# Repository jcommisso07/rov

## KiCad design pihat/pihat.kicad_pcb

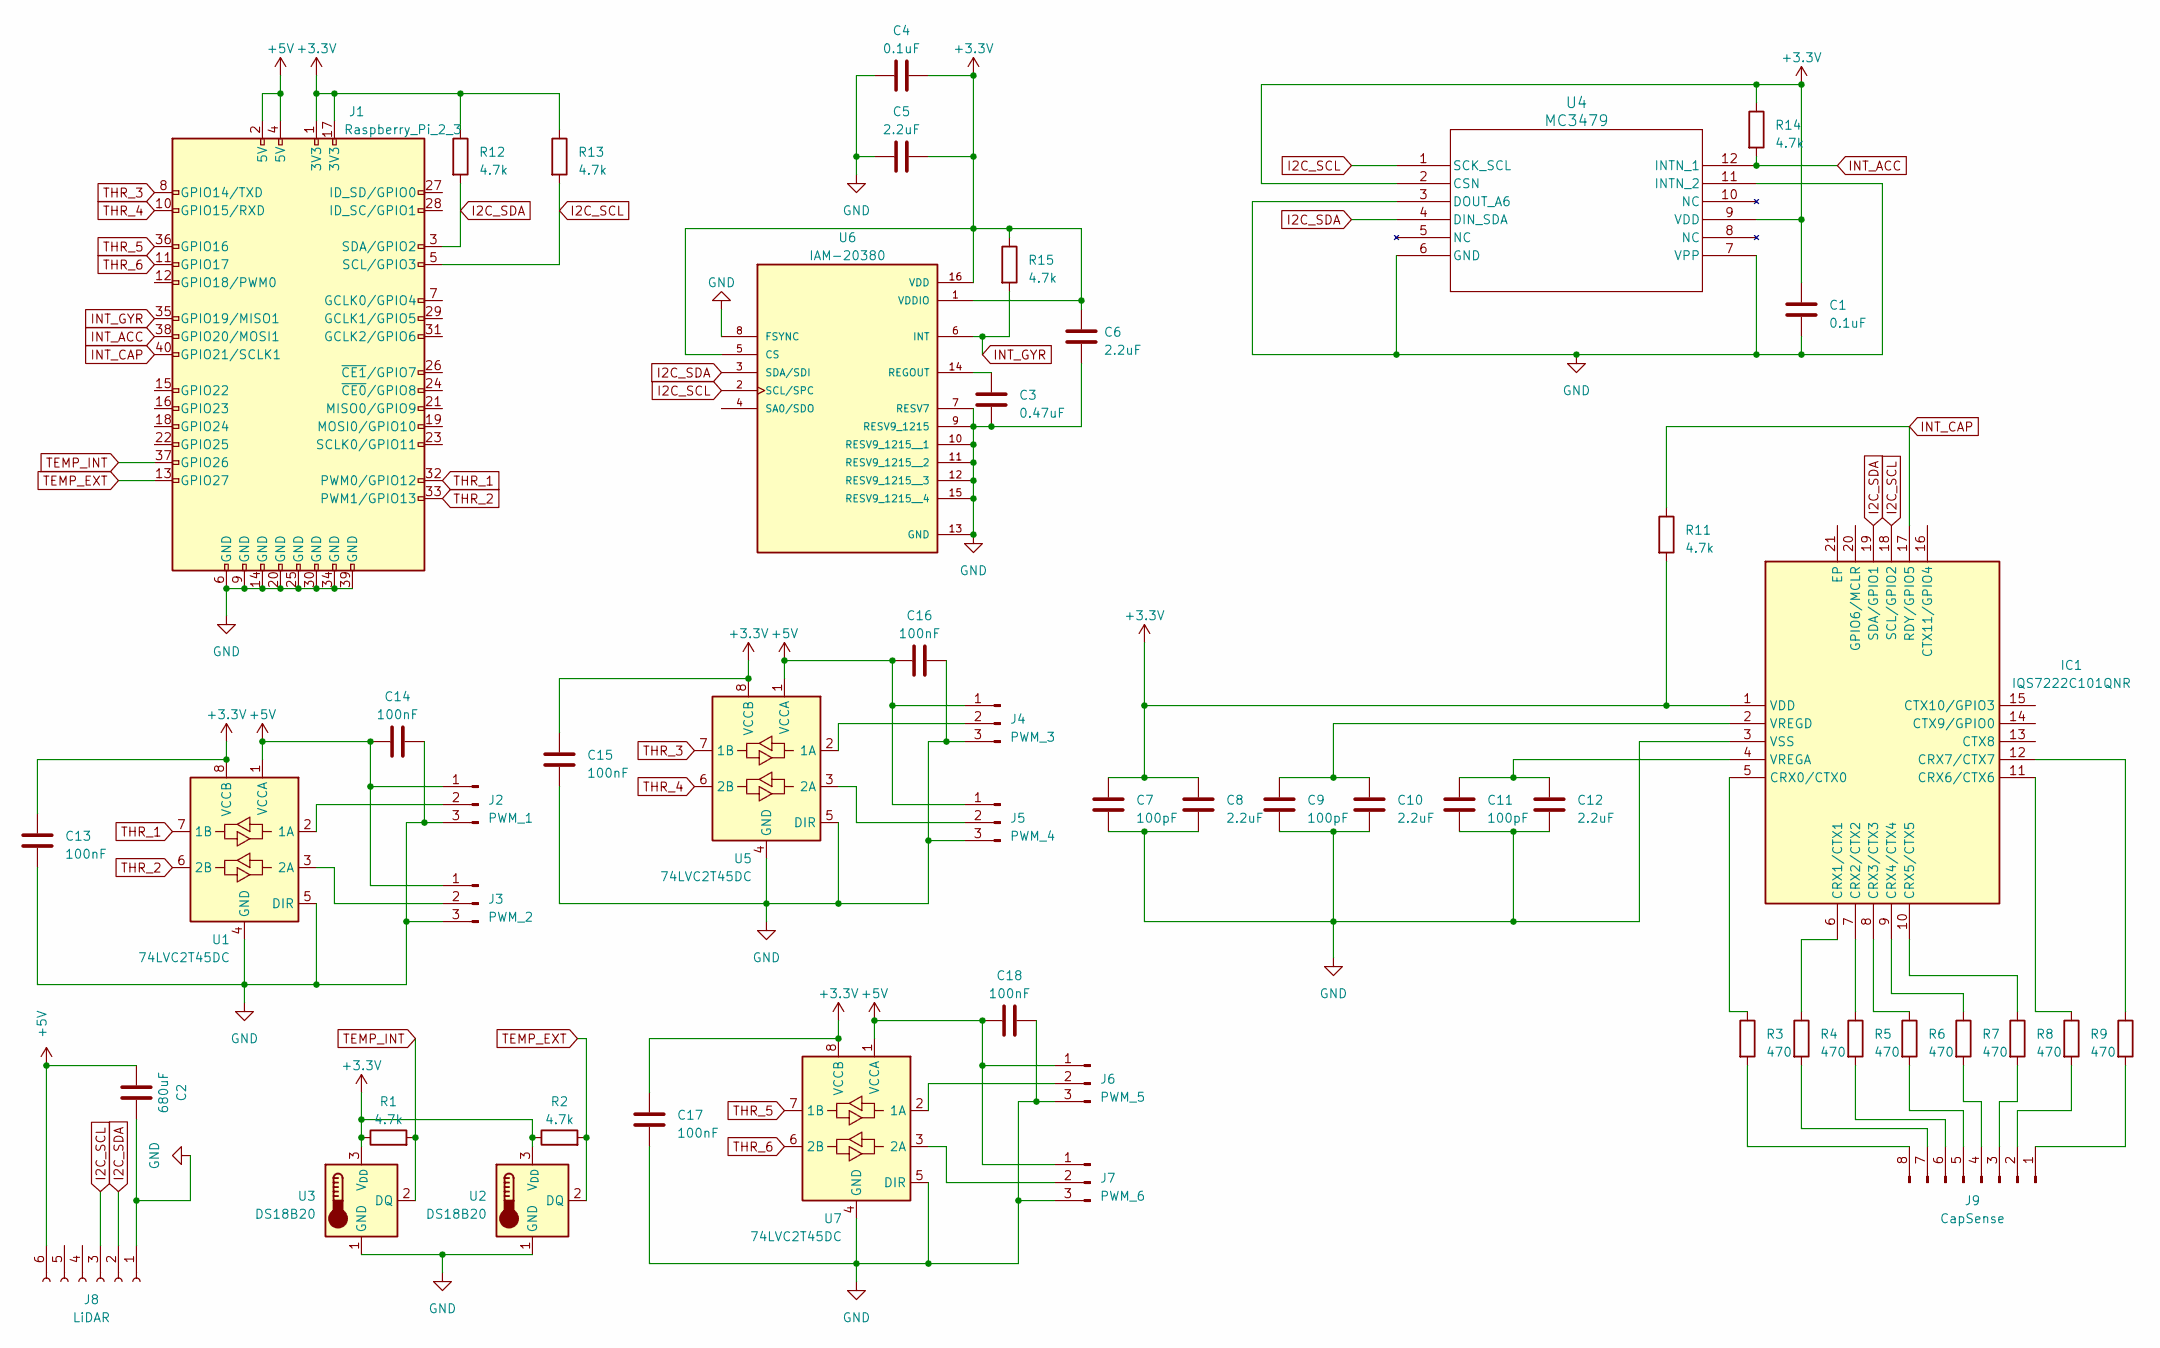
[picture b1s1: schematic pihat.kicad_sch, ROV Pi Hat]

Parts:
C1, C4: 0.1uF; C_0805_2012Metric
C2: 680uF; C_0805_2012Metric
C3: 0.47uF; C_0805_2012Metric
C5, C6, C8, C10, C12: 2.2uF; C_0805_2012Metric
C7, C9, C11: 100pF; C_0805_2012Metric
C13, C14, C15, C16, C17, C18: 100nF; C_0805_2012Metric
IC1: IQS7222C101QNR; QFN40P300X300X60-21N; Mouser Part Number 957-IQS7222C101QNR
J1: Raspberry_Pi_2_3; PinSocket_2x20_P2.54mm_Vertical
J2: PWM_1; PinHeader_1x03_P2.54mm_Vertical
J3: PWM_2; PinHeader_1x03_P2.54mm_Vertical
J4: PWM_3; PinHeader_1x03_P2.54mm_Vertical
J5: PWM_4; PinHeader_1x03_P2.54mm_Vertical
J6: PWM_5; PinHeader_1x03_P2.54mm_Vertical
J7: PWM_6; PinHeader_1x03_P2.54mm_Vertical
J8: LiDAR; PinHeader_1x06_P2.54mm_Vertical
J9: CapSense; PinHeader_1x08_P2.54mm_Vertical
R1, R2, R11, R12, R13, R14, R15: 4.7k; R_0603_1608Metric
R3, R4, R5, R6, R7, R8, R9, R10: 470; R_0603_1608Metric
U1, U5, U7: 74LVC2T45DC; VSSOP-8_2.3x2mm_P0.5mm
U2, U3: DS18B20; PinHeader_1x03_P2.54mm_Vertical
U4: MC3479; MC3479_MEM
U6: IAM-20380; PQFN50P300X300X80-16N

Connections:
+3.3V: C1.1, C4.2, C5.2, C6.2, C7.1, C8.1, C13.1, C15.1, C17.1, IC1.1 (VDD), J1.1 (3V3), J1.17 (3V3), R1.1, R2.1, R11.2, R12.1, R13.1, R14.1, R15.1, U1.8 (VCCB), U2.3 (V_{DD}), U3.3 (V_{DD}), U4.2 (CSN), U4.9 (VDD), U5.8 (VCCB), U6.1 (VDDIO), U6.5 (CS), U6.16 (VDD), U7.8 (VCCB)
+5V: C2.1, C14.1, C16.1, C18.1, J1.2 (5V), J1.4 (5V), J2.1, J3.1, J4.1, J5.1, J6.1, J7.1, J8.6, U1.1 (VCCA), U5.1 (VCCA), U7.1 (VCCA)
GND: C1.2, C2.2, C3.2, C4.1, C5.1, C6.1, C7.2, C8.2, C9.2, C10.2, C11.2, C12.2, C13.2, C14.2, C15.2, C16.2, C17.2, C18.2, IC1.3 (VSS), J1.6 (GND), J1.9 (GND), J1.14 (GND), J1.20 (GND), J1.25 (GND), J1.30 (GND), J1.34 (GND), J1.39 (GND), J2.3, J3.3, J4.3, J5.3, J6.3, J7.3, J8.1, U1.4 (GND), U1.5 (DIR), U2.1 (GND), U3.1 (GND), U4.3 (DOUT_A6), U4.6 (GND), U4.7 (VPP), U4.11 (INTN_2), U5.4 (GND), U5.5 (DIR), U6.7 (RESV7), U6.8 (FSYNC), U6.9 (RESV9_1215), U6.10 (RESV9_1215__1), U6.11 (RESV9_1215__2), U6.12 (RESV9_1215__3), U6.13 (GND), U6.15 (RESV9_1215__4), U7.4 (GND), U7.5 (DIR)
I2C_SCL: IC1.18 (SCL/GPIO2), J1.5 (SCL/GPIO3), J8.3, R13.2, U4.1 (SCK_SCL), U6.2 (SCL/SPC)
I2C_SDA: IC1.19 (SDA/GPIO1), J1.3 (SDA/GPIO2), J8.2, R12.2, U4.4 (DIN_SDA), U6.3 (SDA/SDI)
INT_ACC: J1.38 (GPIO20/MOSI1), R14.2, U4.12 (INTN_1)
INT_CAP: IC1.17 (RDY/GPIO5), J1.40 (GPIO21/SCLK1), R11.1
INT_GYR: J1.35 (GPIO19/MISO1), R15.2, U6.6 (INT)
unnamed: IC1.5 (CRX0/CTX0), R3.1
unnamed: IC1.6 (CRX1/CTX1), R4.1
unnamed: IC1.7 (CRX2/CTX2), R5.1
unnamed: IC1.8 (CRX3/CTX3), R6.1
unnamed: IC1.9 (CRX4/CTX4), R7.1
unnamed: IC1.10 (CRX5/CTX5), R8.1
unnamed: IC1.11 (CRX6/CTX6), R9.1
unnamed: IC1.12 (CRX7/CTX7), R10.1
unnamed: C11.1, C12.1, IC1.4 (VREGA)
unnamed: C9.1, C10.1, IC1.2 (VREGD)
unnamed: J2.2, U1.2 (1A)
unnamed: J3.2, U1.3 (2A)
unnamed: J4.2, U5.2 (1A)
unnamed: J5.2, U5.3 (2A)
unnamed: J6.2, U7.2 (1A)
unnamed: J7.2, U7.3 (2A)
unnamed: J9.1, R10.2
unnamed: J9.2, R9.2
unnamed: J9.3, R8.2
unnamed: J9.4, R7.2
unnamed: J9.5, R6.2
unnamed: J9.6, R5.2
unnamed: J9.7, R4.2
unnamed: J9.8, R3.2
unnamed: C3.1, U6.14 (REGOUT)
TEMP_EXT: J1.13 (GPIO27), R2.2, U2.2 (DQ)
TEMP_INT: J1.37 (GPIO26), R1.2, U3.2 (DQ)
THR_1: J1.32 (PWM0/GPIO12), U1.7 (1B)
THR_2: J1.33 (PWM1/GPIO13), U1.6 (2B)
THR_3: J1.8 (GPIO14/TXD), U5.7 (1B)
THR_4: J1.10 (GPIO15/RXD), U5.6 (2B)
THR_5: J1.36 (GPIO16), U7.7 (1B)
THR_6: J1.11 (GPIO17), U7.6 (2B)

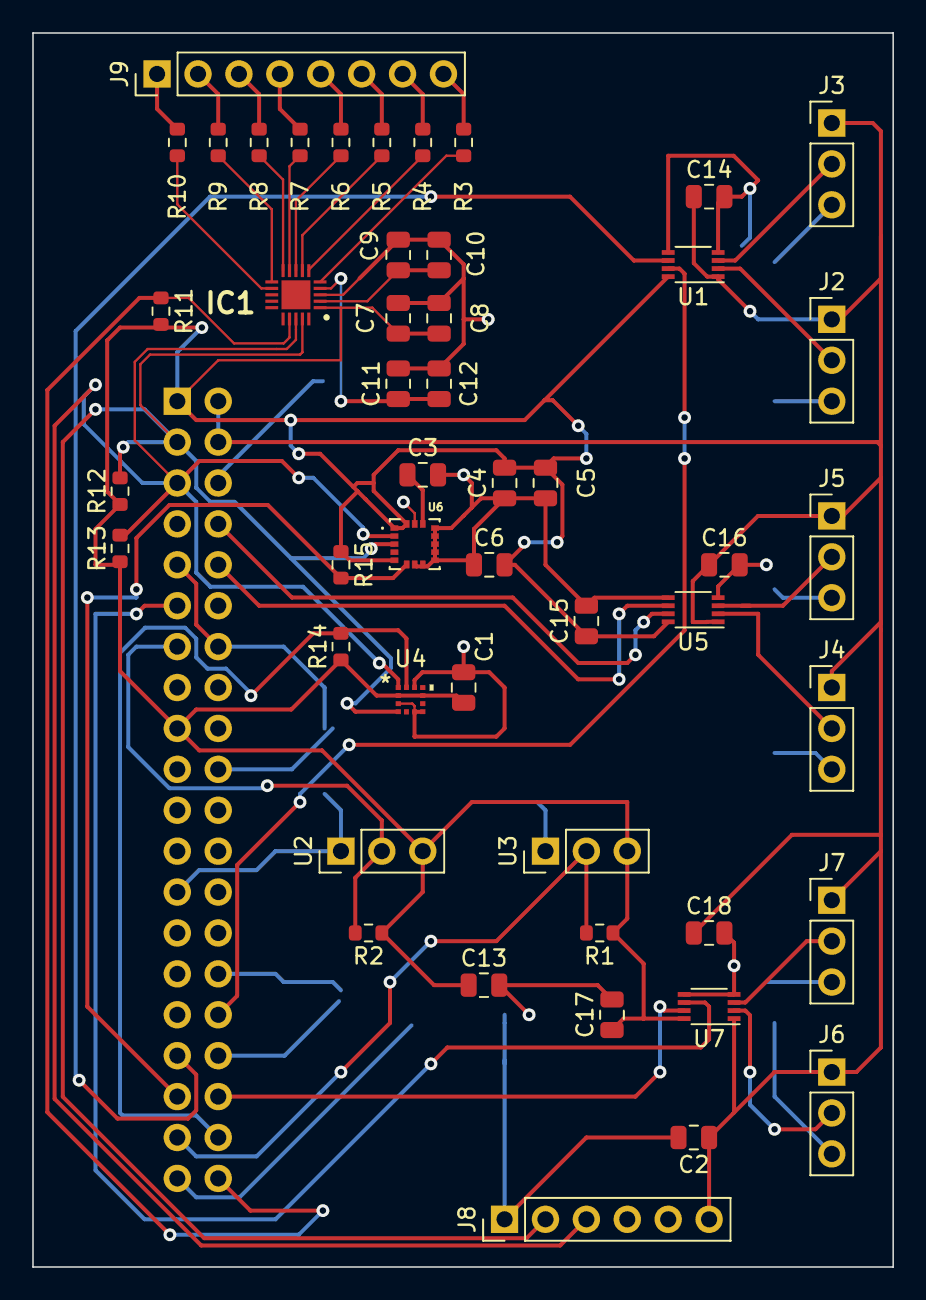
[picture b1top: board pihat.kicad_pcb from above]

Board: 2 copper layers, 53.4 x 76.6 mm, 50 parts (1 on the bottom side), 41 nets.

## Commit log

2024-05-02 added mechanical files
